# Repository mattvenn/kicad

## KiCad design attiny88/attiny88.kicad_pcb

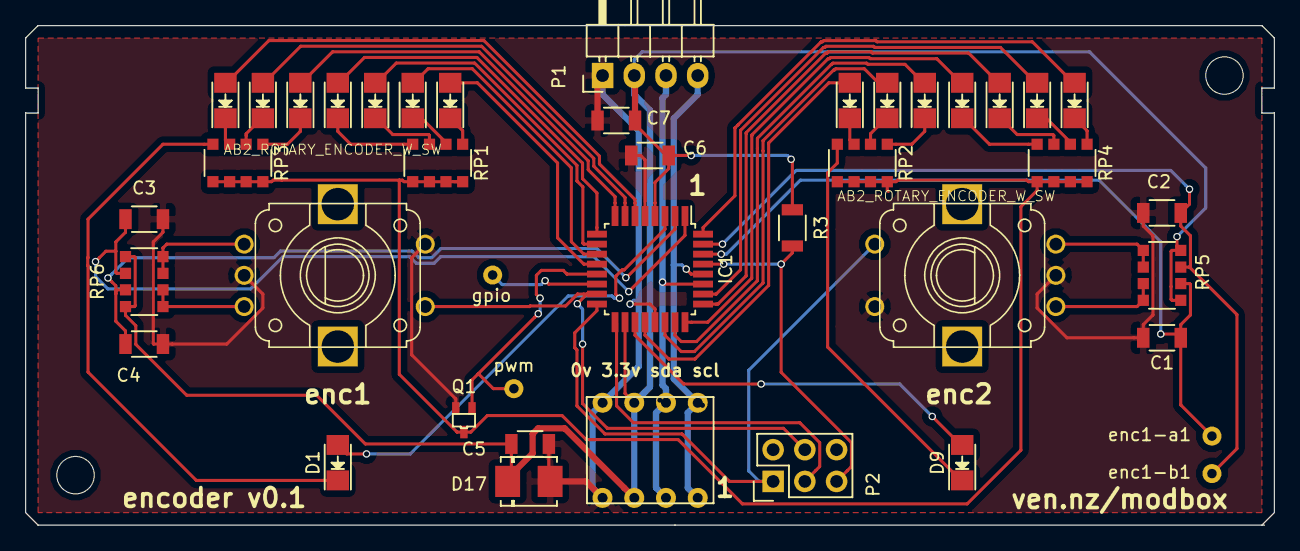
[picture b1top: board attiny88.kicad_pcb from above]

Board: 2 copper layers, 100.0 x 40.0 mm, 42 parts (0 on the bottom side), 51 nets.

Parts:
C1, C2, C3, C4: C; C_1206
C5: 1u; C_1206
C6: 0.1u; C_1206
C7: 10u; C_1206
D1, D2, D3, D4, D5, D6, D7, D8, D9, D10, D11, D12, D13, D14, D15, D16: LED; LED-1206
D17: 1A; DO-214BA
IC1: ATTINY88-A; TQFP-32_7x7mm_Pitch0.8mm
P1: CONN_01X04; Pin_Header_Angled_1x04
P2: CONN_02X03; Pin_Header_Straight_2x03
P3: CONN_01X04; molex 4way cgrid
Q1: MMBF170; SOT-323
R3: 20k; R_1206
ROT_ENC1, ROT_ENC2: AB2_ROTARY_ENCODER_W_SW; AB2_ROTARY_ENCODER_W_SWITCH
RP1, RP2, RP3, RP4, RP5, RP6: 220; R_Array_Convex_4x1206
enc1-a1, enc1-b1: testpoint
gpio: testpoint
pwm: gpio; testpoint

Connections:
+3V3: C5.1, C6.1, C7.1, D17.1, IC1.4, IC1.18, P1.2, P3.2, R3.1, RP5.5, RP5.8, RP6.5, RP6.8
Earth: C1.1, C2.2, C3.1, C4.2, C5.2, C6.2, C7.2, D17.2, IC1.5, IC1.21, P1.1, P2.6, P3.1, Q1.2, ROT_ENC1.2, ROT_ENC1.6, ROT_ENC2.2, ROT_ENC2.6
unnamed: D1.1, RP3.4
unnamed: D2.1, RP3.3
unnamed: D3.1, RP3.2
unnamed: D4.1, RP3.1
unnamed: D5.1, RP1.4
unnamed: D6.1, RP1.3
unnamed: D7.1, RP1.2
unnamed: D8.1, RP1.1
unnamed: D9.1, RP2.4
unnamed: D10.1, RP2.3
unnamed: D11.1, RP2.2
unnamed: D12.1, RP2.1
unnamed: D13.1, RP4.4
unnamed: D14.1, RP4.3
unnamed: D15.1, RP4.2
unnamed: D16.1, RP4.1
unnamed: Q1.3, RP1.5, RP1.6, RP1.7, RP1.8, RP2.5, RP2.6, RP2.7, RP2.8, RP3.5, RP3.6, RP3.7, RP3.8, RP4.5, RP4.6, RP4.7, RP4.8
unnamed: ROT_ENC1.1, RP6.3, RP6.4
unnamed: ROT_ENC1.3, RP6.1, RP6.2
unnamed: ROT_ENC2.1, RP5.3, RP5.4
unnamed: ROT_ENC2.3, RP5.1, RP5.2
enc1-a: C1.2, IC1.30, RP5.6, enc1-a1.1
enc1-b: C2.1, IC1.31, RP5.7, enc1-b1.1
enc2-a: C3.2, IC1.1, RP6.6
enc2-b: C4.1, IC1.2, RP6.7
enc2-s: IC1.15, P2.4, ROT_ENC1.4
gpio1: IC1.14, gpio.1
led0: D1.2, IC1.3
led1: D2.2, IC1.6
led2: D3.2, IC1.7
led3: D4.2, IC1.8
led4: D5.2, IC1.9
led5: D6.2, IC1.10
led6: D7.2, IC1.11
led7: D8.2, IC1.12
led8: D9.2, IC1.19
led9: D10.2, IC1.20
led10: D11.2, IC1.22
led11: D12.2, IC1.23
led12: D13.2, IC1.24
led13: D14.2, IC1.25
led14: D15.2, IC1.26
led15: D16.2, IC1.32
miso: IC1.16, P2.1, ROT_ENC2.4
pwm: IC1.13, Q1.1, pwm.1
reset: IC1.29, P2.5, R3.2
sck: IC1.17, P2.3
scl: IC1.28, P1.4, P3.4
sda: IC1.27, P1.3, P3.3

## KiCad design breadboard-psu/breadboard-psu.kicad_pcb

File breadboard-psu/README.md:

# KiCad workshop handout

Shortlink to this page: ven.nz/kicad-ws

The documentation for this workshop mostly consists of [youtube
screencasts](https://www.youtube.com/playlist?list=PLmcDgdDpcaPjIBy60y22XzG036ckQI7bC). The
screencasts are deliberately fast, if you need them slower then click the video's settings button and choose a slower speed.

You are advised to watch the screencasts all the way through before starting,
then reference them as needed.

Each screencast has a clickable table of contents. Click the video's 'show more' link to expose it.

The screencasts show the creation of a simple LED board as a way of showing the
process. Don't just follow along - you will be making a breadboard power supply to supply either 3.3v or 5v.

# Drawing the Schematic

[Watch the schematic creation screencast](https://www.youtube.com/watch?v=v-qCI8wv72w&list=PLmcDgdDpcaPjIBy60y22XzG036ckQI7bC&index=1)

Your first task is to produce the schematic below.
If you want a 3.3v output use part AP1117D33. If you want 5v then use LM7805CT.

## Tips

* Don't bother naming components, that will happen automatically when you
 'annotate components'
* The regulator footprint is in the power_integrations library
* Use the hot keys below!

## Hot Keys

* ? - show hotkeys
* e - edit component
* m - move component (without wires)
* g - drag component (with wires)
* r - rotate
* a - add component
* del - delete component
* w - start a wire
* c - copy
* l - lable a wire (wires with the same label are joined)

## Adding a library

The barrel jack's PCB footprint will not be fabricated properly because
OSHPark's fab don't allow thin slots. You'll use a different footprint that uses
large holes instead.

Download the [barrel jack's modified footprint library](https://github.com/mattvenn/kicad/raw/master/breadboard-psu/barrel.zip)

Footprint libraries are a directory containing 1 or more footprint
files. The directory name ends in .pretty. The footprint files end in
.kicad_mod.

* open Eschema, run CvPCB to associate footprints
* preferences -> footprint libraries
* either project specific or global tab
* add the path to the library directory (ends in .pretty) ensure its type is kicad
* scroll down the list of libraries and click the new barrel library
* highlight the barrel jack component in the middle column and double click the
 new footprint on the right column.

# Create the PCB

[Watch the PCB creation screencast](https://www.youtube.com/watch?v=g9wKArt-YmE&index=2&list=PLmcDgdDpcaPjIBy60y22XzG036ckQI7bC)

Example layout of the PCB:

## Tips

* Some operations are easier in default canvas (F9), others in OpenGL (F11)
* Use the hot keys below!

## Kot Keys

* ? - show hotkeys
* space - reset local co-ordinates
* F1 - zoom in
* F2 - zoom out
* m - move component (without wires)
* g - drag component (with wires)
* del - delete an object
* F11 - switch to openGL view (necessary for push'n'shove routing)
* e - routing options (only in openGL)
* x - start routing
* pg up - route on top layer
* pg down - route on bottom layer
* v - create via
* f - flip a component between top & bottom layers

# Fabrication

[Watch the fabrication screencast](https://www.youtube.com/watch?v=VwQu3Ap_2rI&list=PLmcDgdDpcaPjIBy60y22XzG036ckQI7bC&index=5)

## Description of layers

* F.Cu - top copper layer used for electrical connections
* B.Cu - bottom copper layer (as above)
* F.SilkS - top silk screen used for component markings and orientation
* B.SilkS - bottom silk screen (as above)
* F.Mask - top mask used to cover the electrical connections with a nonconductive coloured layer
* B.Mask - bottom mask (as above)
* Edge.Cuts - where the board should be cut out

Each of these layers is exported as a separate file called a gerber.

You also need a drill file that specifies where all the holes are.

Zip all the files together and then upload to [OSHPark.com](http://oshpark.com)

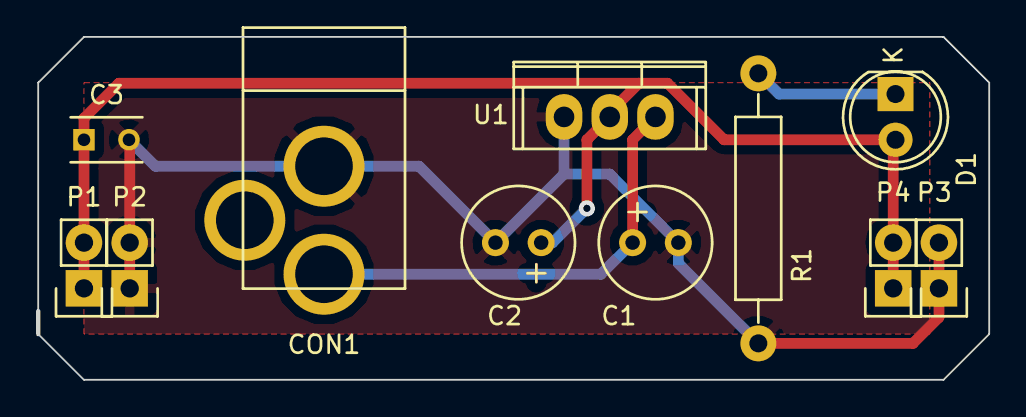
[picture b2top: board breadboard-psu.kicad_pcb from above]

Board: 2 copper layers, 52.8 x 19.0 mm, 11 parts (0 on the bottom side), 4 nets.

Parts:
C1, C2: 10uf; Elko_vert_11.2x6.3mm_RM2.5
C3: 0.1uf; C_Rect_L4_W2.5_P2.5
CON1: BARREL_JACK
D1: LED; LED-5MM
P1, P4: +; Pin_Header_Straight_1x02
P2, P3: -; Pin_Header_Straight_1x02
R1: 200R; Resistor_Horizontal_RM15mm
U1: AP1117D33; TO-220

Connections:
+3V3: C2.1, C3.1, D1.2, P1.1, P1.2, P4.1, P4.2, U1.2
+5V: C1.1, CON1.1, U1.3
GND: C1.2, C2.2, C3.2, CON1.2, P2.1, P2.2, P3.1, P3.2, R1.2, U1.1
unnamed: D1.1, R1.1

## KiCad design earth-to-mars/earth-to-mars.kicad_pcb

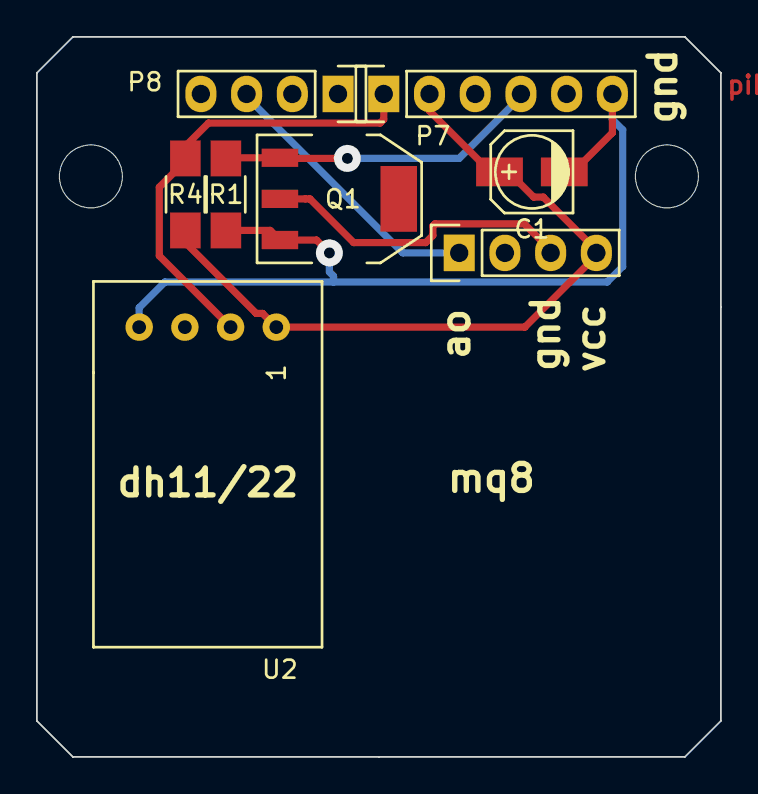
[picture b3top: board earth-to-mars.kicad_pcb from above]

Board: 2 copper layers, 38.0 x 40.0 mm, 8 parts (0 on the bottom side), 6 nets.

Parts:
C1: 4.7uf; c_elec_4x4.5
P1, P8: CONN_01X04; Pin_Header_Straight_1x04
P7: CONN_01X06; Pin_Header_Straight_1x06
Q1: Q_NMOS_DGS; SOT-223
R1: 4k7; R_1206_HandSoldering
R4: 4.7k; R_1206_HandSoldering
U2: dht11

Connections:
+5V: C1.1, P1.4, P7.2, R4.1, U2.1
Earth: C1.2, P7.6, Q1.3, R1.2, U2.4
unnamed: P1.3, Q1.1
mega_adc6: P1.1, P8.3
mega_io11_mosi: P7.4, Q1.2, R1.1
mega_io12_miso: P7.1, R4.2, U2.2

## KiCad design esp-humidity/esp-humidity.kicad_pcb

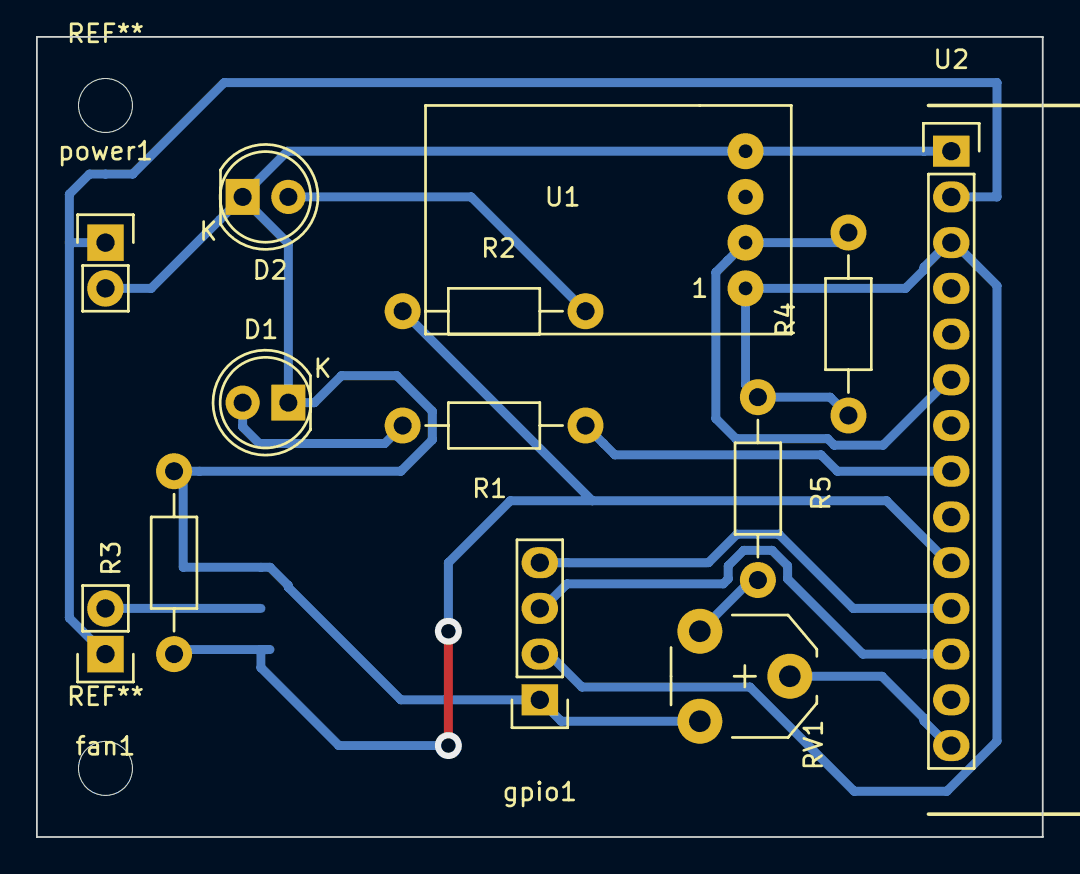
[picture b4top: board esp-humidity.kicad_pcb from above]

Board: 2 copper layers, 55.9 x 44.5 mm, 14 parts (1 on the bottom side), 13 nets.

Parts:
D1, D2: LED; LED-5MM
Q1: BUK98150-55A; SOT-223
R1, R2, R3, R4, R5: R; Resistor_Horizontal_RM10mm
RV1: POT; Potentiometer_VishaySpectrol-Econtrim-Type36M
U1: dht11
U2: esp8266-breakout; Pin_Header_Straight_1x14
fan1: CONN_01X02; Pin_Header_Straight_1x02
gpio1: CONN_01X04; Pin_Header_Straight_1x04
power1: CONN_01X02; Pin_Header_Straight_1x02

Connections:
+3V3: R4.1, R5.1, U1.1, U2.3, gpio1.2
+12V: U2.2, fan1.1, power1.1
/dht11-data: R4.2, U1.2, U2.6
/fan: Q1.1, R2.1, R3.1, U2.10
/gpio1: U2.11, gpio1.4
/gpio2: U2.12, gpio1.3
/status: R1.1, U2.8
Earth: D1.1, D2.1, Q1.3, R3.2, RV1.3, U1.4, U2.1, gpio1.1, power1.2
unnamed: D1.2, R1.2
unnamed: D2.2, R2.2
unnamed: Q1.2, fan1.2
unnamed: R5.2, RV1.1
unnamed: RV1.2, U2.14

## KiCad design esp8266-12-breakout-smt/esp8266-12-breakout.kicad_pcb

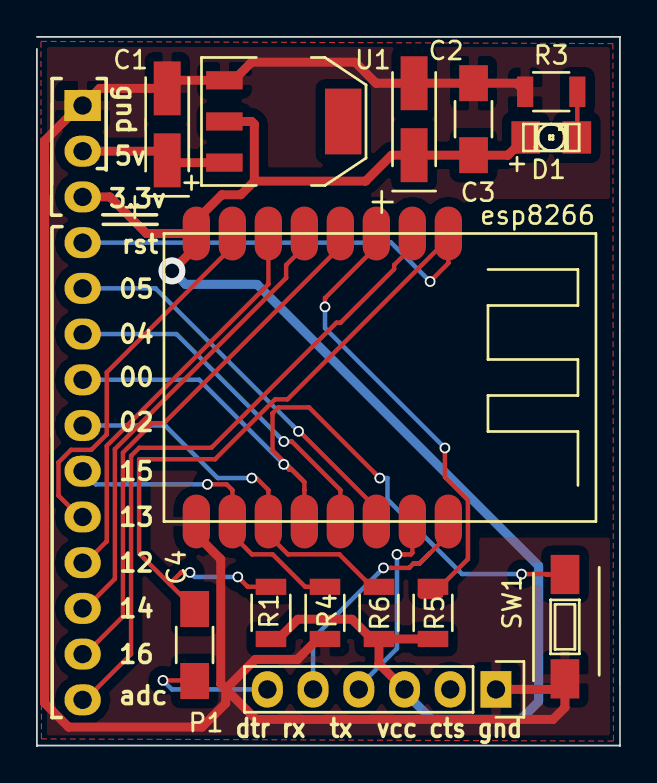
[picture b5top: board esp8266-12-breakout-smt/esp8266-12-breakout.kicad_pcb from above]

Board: 2 copper layers, 32.4 x 39.4 mm, 15 parts (1 on the bottom side), 19 nets.

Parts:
C1, C2: 10uf; TantalC_SizeA_EIA-3216_HandSoldering
C3: 0.1uf; C_1206_HandSoldering
C4: 1uf; C_1206_HandSoldering
D1: LED; LED-1206
P1: ftdi; Pin_Header_Straight_1x06
P2: CONN_01X14; Pin_Header_Straight_1x14
R1, R4, R5, R6: 10k; R_1206
R3: 68r; R_1206
SW1: SW_PUSH; SW_SPST_FSMSM
U1: AP1117D33; SOT-223
esp8266: U2; esp8266-12

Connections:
+3V3: C2.1, C3.1, D1.2, P1.3, P2.3, R1.1, R4.1, R5.1, U1.2, esp8266.8
+5V: C1.1, P2.2, U1.3
/adc: P2.14, esp8266.2
/ch_pd: R5.2, esp8266.3
/gpio0: P2.7, SW1.1, esp8266.12
/gpio2: P2.8, R4.2, esp8266.11
/gpio4: P2.6, esp8266.13
/gpio5: P2.5, esp8266.14
/gpio12: P2.11, esp8266.6
/gpio13: P2.10, esp8266.7
/gpio14: P2.12, esp8266.5
/gpio15: P2.9, R6.1, esp8266.10
/gpio16: P2.13, esp8266.4
/reset: C4.2, P2.4, R1.2, esp8266.1
/rx: P1.4, esp8266.15
/tx: P1.5, esp8266.16
GND: C1.2, C2.2, C3.2, P1.1, P2.1, R3.2, R6.2, SW1.2, U1.1, esp8266.9
unnamed: C4.1, P1.6
unnamed: D1.1, R3.1

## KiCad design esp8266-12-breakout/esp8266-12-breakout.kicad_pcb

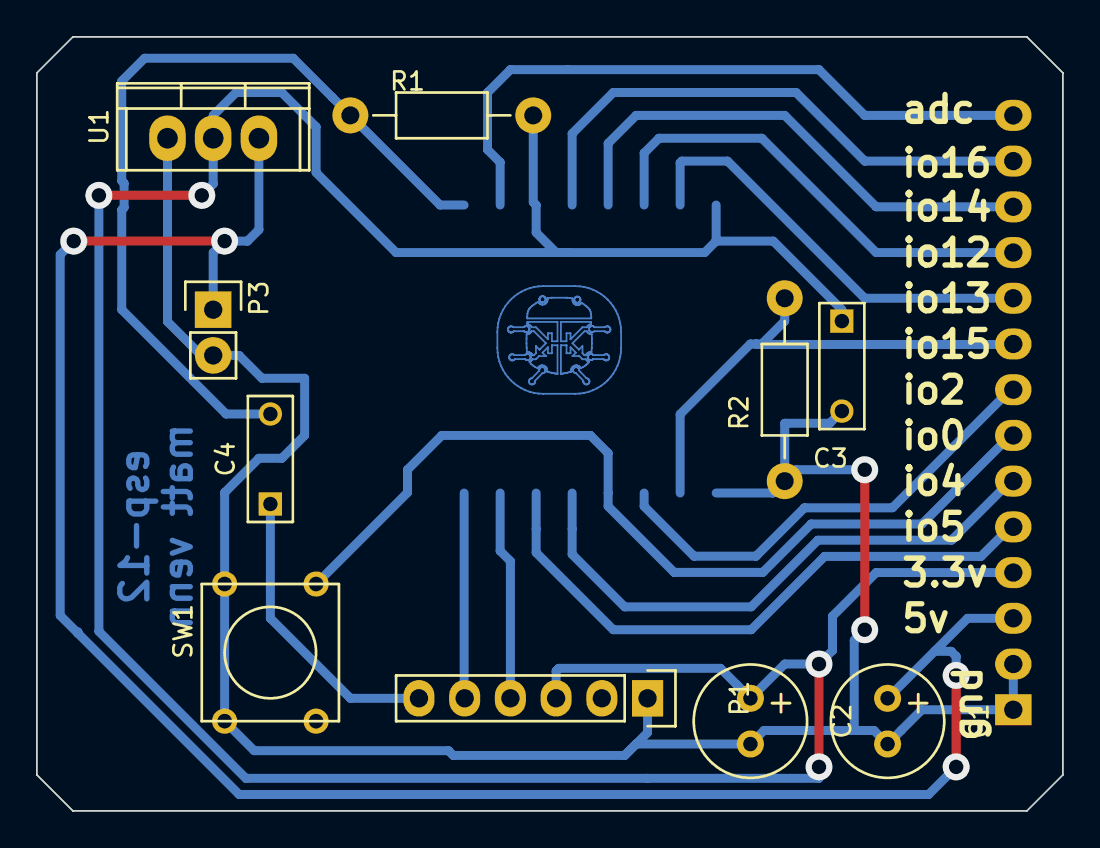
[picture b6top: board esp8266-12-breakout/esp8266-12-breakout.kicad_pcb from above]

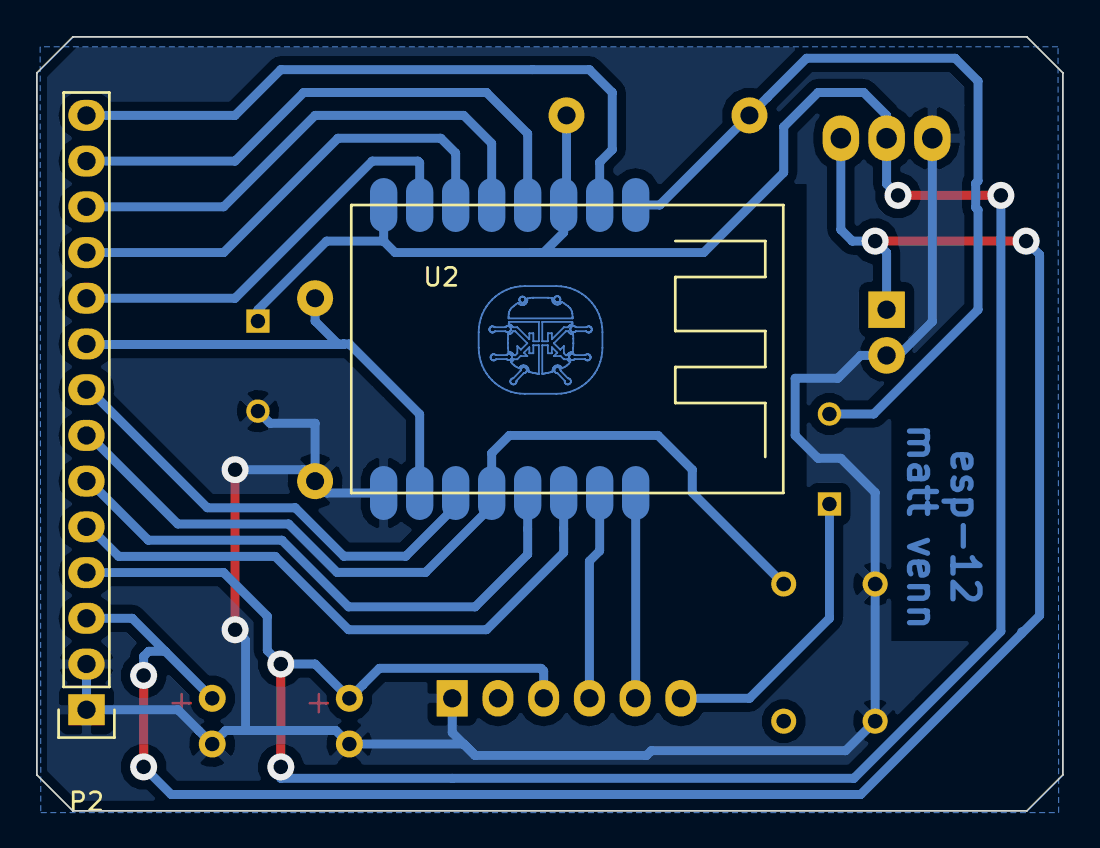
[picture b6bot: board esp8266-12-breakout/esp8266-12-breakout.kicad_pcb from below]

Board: 2 copper layers, 57.0 x 43.0 mm, 12 parts (2 on the bottom side), 17 nets.

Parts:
C1, C2: 10uf; Elko_vert_11.2x6.3mm_RM2.5
C3: 0.1uf; C_Rect_L7_W2.5_P5
C4: 1uf; C_Rect_L7_W2.5_P5
P1: ftdi; Pin_Header_Straight_1x06
P2: CONN_01X14; Pin_Header_Straight_1x14
P3: power; Pin_Header_Straight_1x02
R1, R2: 10k; Resistor_Horizontal_RM10mm
SW1: SW_PUSH; SW_PUSH_SMALL
U1: AP1117D33; TO-220
U2: esp8266-12

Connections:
+3V3: C2.1, C3.1, P1.3, P2.4, R1.1, U1.2, U2.3, U2.8
+5V: C1.1, P2.3, P3.1, U1.3
/adc: P2.14, U2.2
/gpio0: P2.7, SW1.1, U2.12
/gpio2: P2.8, U2.11
/gpio4: P2.6, U2.13
/gpio5: P2.5, U2.14
/gpio12: P2.11, U2.6
/gpio13: P2.10, U2.7
/gpio14: P2.12, U2.5
/gpio15: P2.9, R2.1, U2.10
/gpio16: P2.13, U2.4
/reset: C4.2, R1.2, U2.1
/rx: P1.4, U2.15
/tx: P1.5, U2.16
GND: C1.2, C2.2, C3.2, P1.1, P2.1, P2.2, P3.2, R2.2, SW1.2, U1.1, U2.9
unnamed: C4.1, P1.6

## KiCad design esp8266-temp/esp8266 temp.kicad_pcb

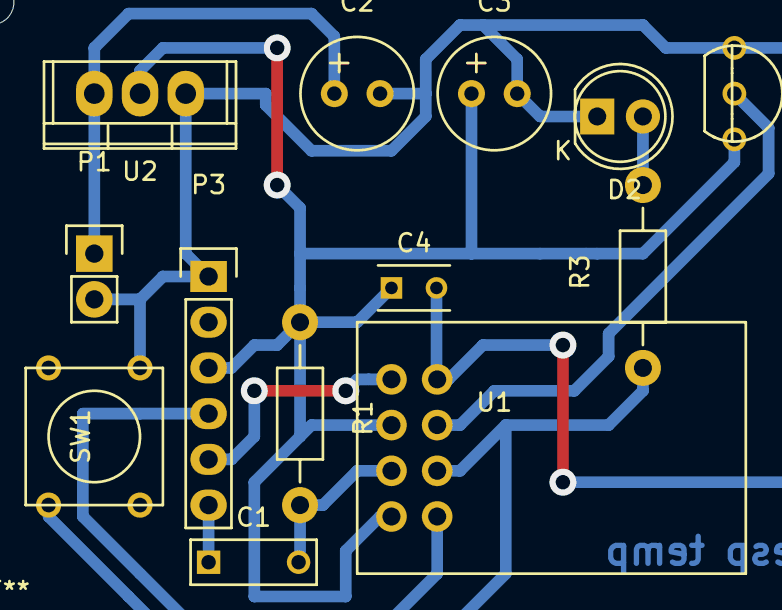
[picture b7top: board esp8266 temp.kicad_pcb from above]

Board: 2 copper layers, 13 parts (0 on the bottom side), 10 nets.

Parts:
C1: 1uf; C_Rect_L7_W2.5_P5
C2, C3: 10uf; Elko_vert_11.2x6.3mm_RM2.5
C4: 0.1uf; C_Rect_L4_W2.5_P2.5
D2: LED; LED-5MM
IC1: DS18B20; 1wire-TO92-
P1: power; Pin_Header_Straight_1x02
P3: ftdi; Pin_Header_Straight_1x06
R1: 10k; Resistor_Horizontal_RM10mm
R3: 1k; Resistor_Horizontal_RM10mm
SW1: SW_PUSH; SW_PUSH_SMALL
U1: esp8266
U2: AP1117D33; TO-220

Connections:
+3V3: C3.1, C4.1, IC1.3, P3.3, R1.1, U1.2, U1.6, U2.2
+5V: C2.1, P1.1, U2.3
/gpio0: R3.1, SW1.1, U1.3
/gpio2: IC1.2, U1.5
/reset: C1.2, R1.2, U1.4
/rx: P3.4, U1.1
/tx: P3.5, U1.8
GND: C2.2, C3.2, C4.2, D2.1, IC1.1, P1.2, P3.1, SW1.2, U1.7, U2.1
unnamed: C1.1, P3.6
unnamed: D2.2, R3.2

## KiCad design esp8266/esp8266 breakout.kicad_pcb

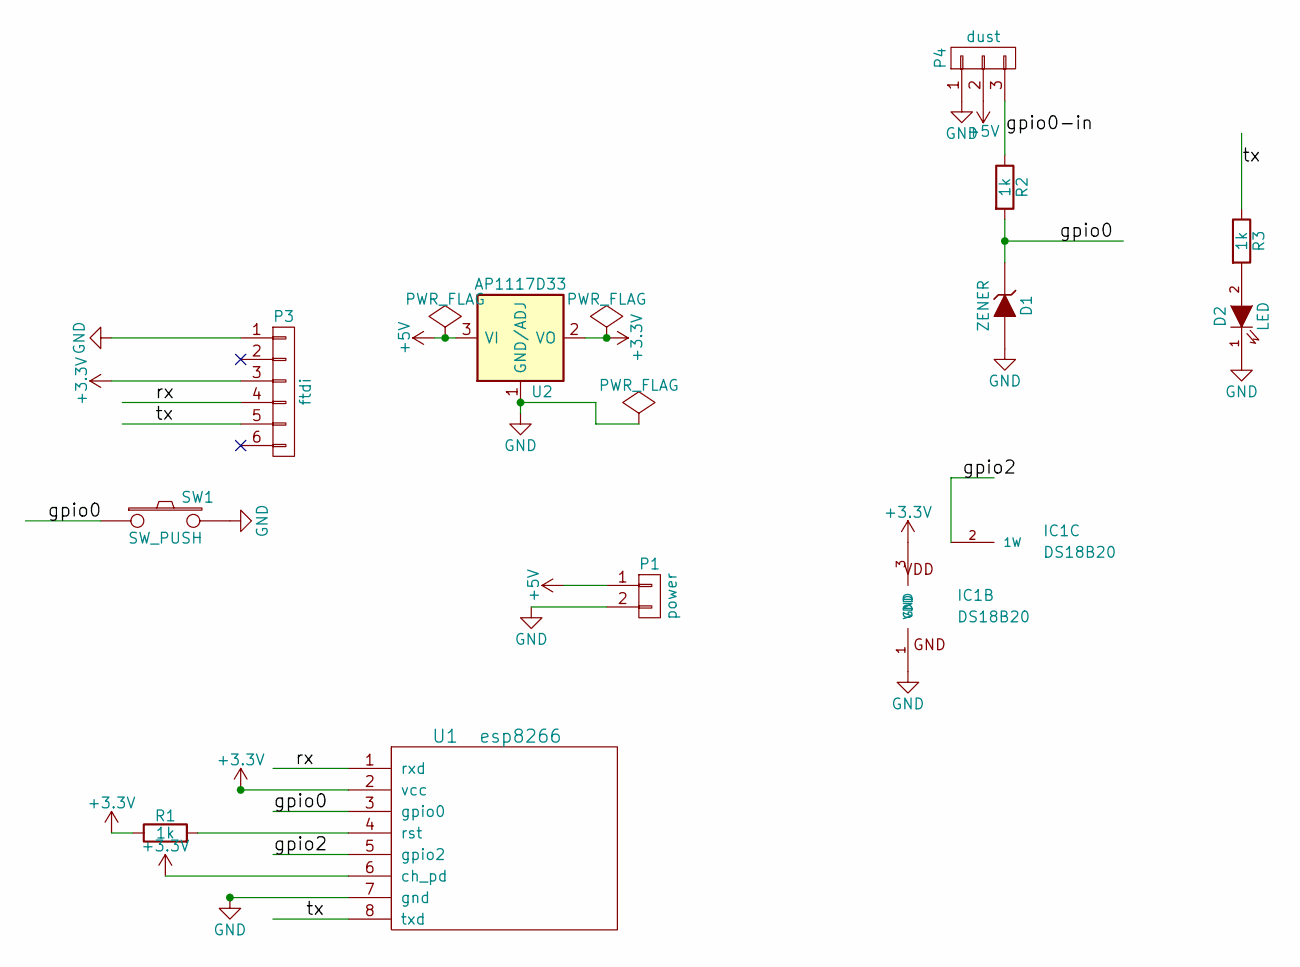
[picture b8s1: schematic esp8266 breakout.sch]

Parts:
D1: ZENER; D3
D2: LED; LED-5MM
IC1: DS18B20; 1wire-TO92-
P1: power; Pin_Header_Straight_1x02
P3: ftdi; Pin_Header_Straight_1x06
P4: dust; Pin_Header_Straight_1x03
R1, R2, R3: 1k; Resistor_Horizontal_RM10mm
SW1: SW_PUSH; SW_PUSH_SMALL
U1: esp8266
U2: AP1117D33; TO-220

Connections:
+3V3: IC1.3 (VDD), P3.3, R1.1, U1.2 (vcc), U1.6 (ch_pd), U2.2 (VO)
+5V: P1.1, P4.2, U2.3 (VI)
/gpio0: D1.1 (K), R2.2, SW1.1, U1.3 (gpio0)
/gpio0-in: P4.3, R2.1
/gpio2: IC1.2 (1W), U1.5 (gpio2)
/rx: P3.4, U1.1 (rxd)
/tx: P3.5, R3.1, U1.8 (txd)
GND: D1.2 (A), D2.1 (K), IC1.1 (GND), P1.2, P3.1, P4.1, SW1.2, U1.7 (gnd), U2.1 (GND/ADJ)
unnamed: D2.2 (A), R3.2
unnamed: R1.2, U1.4 (rst)

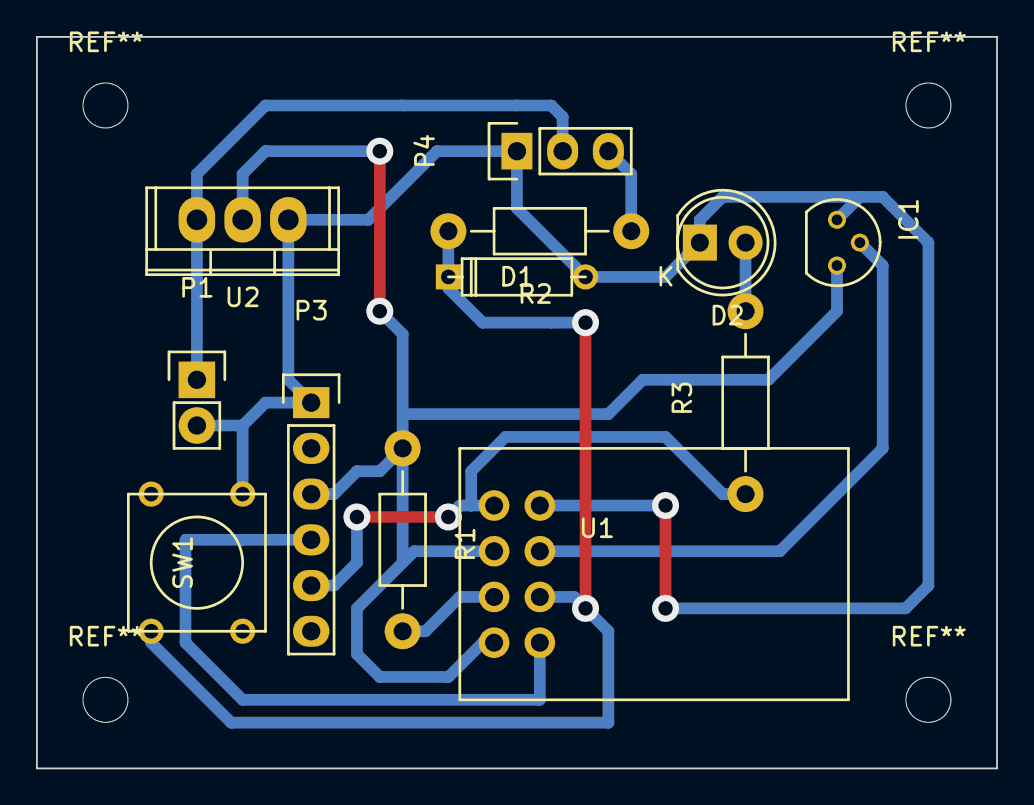
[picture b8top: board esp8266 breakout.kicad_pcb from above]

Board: 2 copper layers, 53.3 x 40.6 mm, 12 parts (0 on the bottom side), 10 nets.
